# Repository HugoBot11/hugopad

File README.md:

# Hugopad
# Overall design 
# Schematic  
# PCB  
# PCB 3D view  
# Case top half 
# Case bottom half 
# BOM  

I nade this macropad for Hack Club's Highway and Hackpad You Ship We Ship projects. It took me a while and I had to redo a lot of things, but I got here!

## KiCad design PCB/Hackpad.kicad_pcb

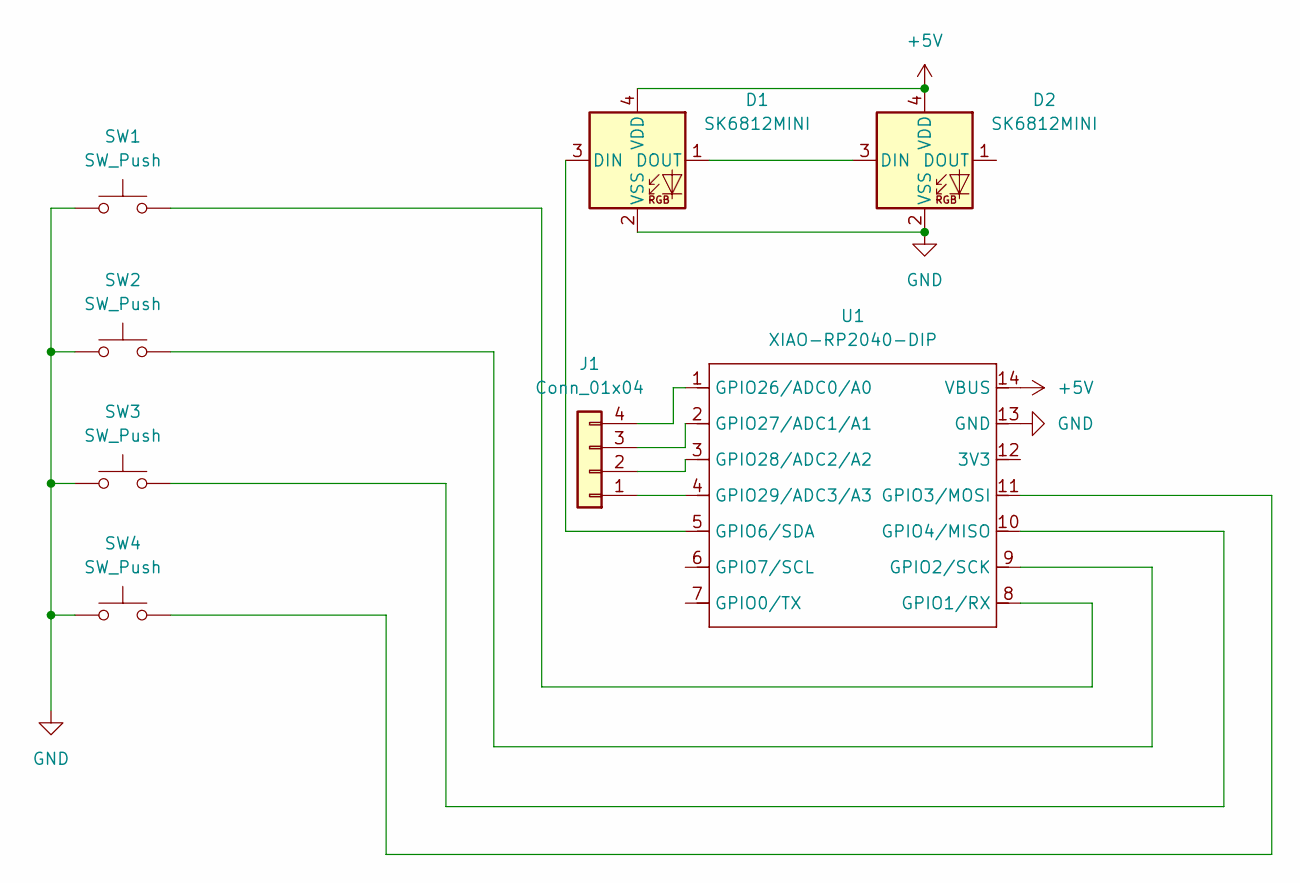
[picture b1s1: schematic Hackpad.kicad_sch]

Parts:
D1, D2: SK6812MINI; LED_SK6812MINI_PLCC4_3.5x3.5mm_P1.75mm
J1: Conn_01x04; SSD1306-0.91-OLED-4pin-128x32
SW1, SW2, SW3, SW4: SW_Push; SW_Cherry_MX_1.00u_PCB
U1: XIAO-RP2040-DIP

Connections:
+5V: D1.4 (VDD), D2.4 (VDD), U1.14 (VBUS)
GND: D1.2 (VSS), D2.2 (VSS), SW1.1, SW2.1, SW3.1, SW4.1, U1.13 (GND)
unnamed: D1.3 (DIN), U1.5 (GPIO6/SDA)
unnamed: D1.1 (DOUT), D2.3 (DIN)
unnamed: J1.1, U1.4 (GPIO29/ADC3/A3)
unnamed: J1.2, U1.3 (GPIO28/ADC2/A2)
unnamed: J1.3, U1.2 (GPIO27/ADC1/A1)
unnamed: J1.4, U1.1 (GPIO26/ADC0/A0)
unnamed: SW1.2, U1.8 (GPIO1/RX)
unnamed: SW2.2, U1.9 (GPIO2/SCK)
unnamed: SW4.2, U1.11 (GPIO3/MOSI)
unnamed: SW3.2, U1.10 (GPIO4/MISO)

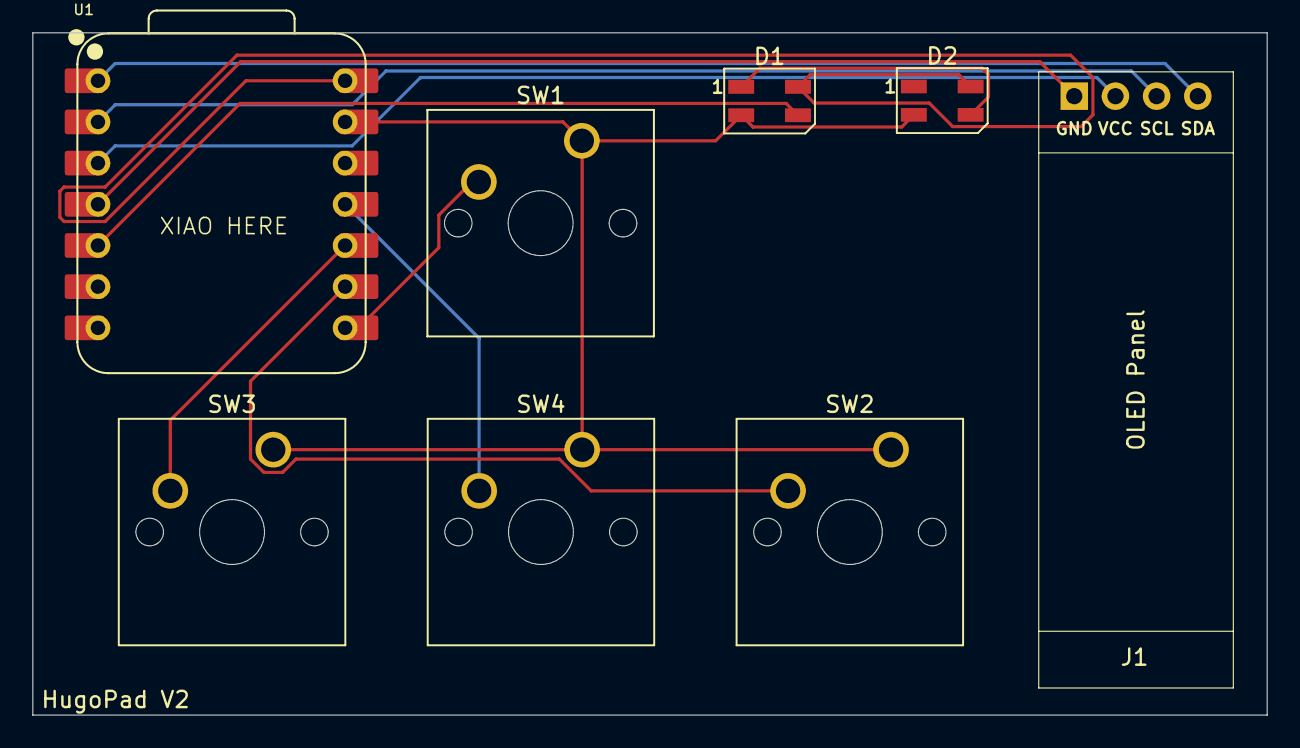
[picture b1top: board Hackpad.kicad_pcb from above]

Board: 2 copper layers, 76.1 x 42.1 mm, 8 parts (0 on the bottom side), 12 nets.

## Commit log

2025-07-31 added files
2025-07-31 Added more files Added more files
2025-08-07 Final commit
